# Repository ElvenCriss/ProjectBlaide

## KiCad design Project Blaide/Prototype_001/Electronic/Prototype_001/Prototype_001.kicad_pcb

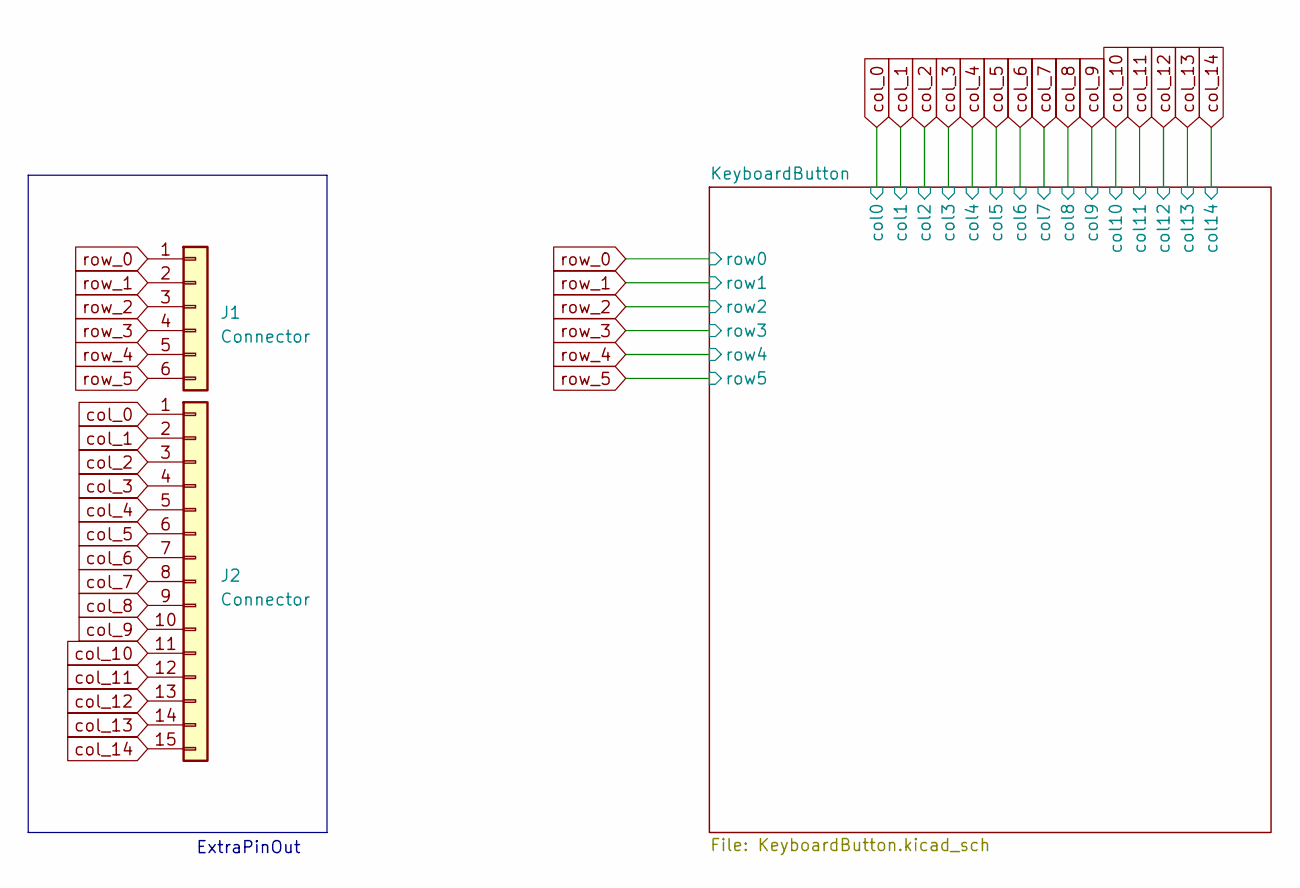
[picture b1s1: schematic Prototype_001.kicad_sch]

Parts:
J1: Connector; PinHeader_1x06_P2.54mm_Vertical
J2: Connector; PinHeader_1x15_P2.54mm_Vertical

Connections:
col_0: J2.1; also elsewhere on the board
col_1: J2.2; also elsewhere on the board
col_2: J2.3; also elsewhere on the board
col_3: J2.4; also elsewhere on the board
col_4: J2.5; also elsewhere on the board
col_5: J2.6; also elsewhere on the board
col_6: J2.7; also elsewhere on the board
col_7: J2.8; also elsewhere on the board
col_8: J2.9; also elsewhere on the board
col_9: J2.10; also elsewhere on the board
col_10: J2.11; also elsewhere on the board
col_11: J2.12; also elsewhere on the board
col_12: J2.13; also elsewhere on the board
col_13: J2.14; also elsewhere on the board
col_14: J2.15; also elsewhere on the board
row_0: J1.1; also elsewhere on the board
row_1: J1.2; also elsewhere on the board
row_2: J1.3; also elsewhere on the board
row_3: J1.4; also elsewhere on the board
row_4: J1.5; also elsewhere on the board
row_5: J1.6; also elsewhere on the board

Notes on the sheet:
ExtraPinOut

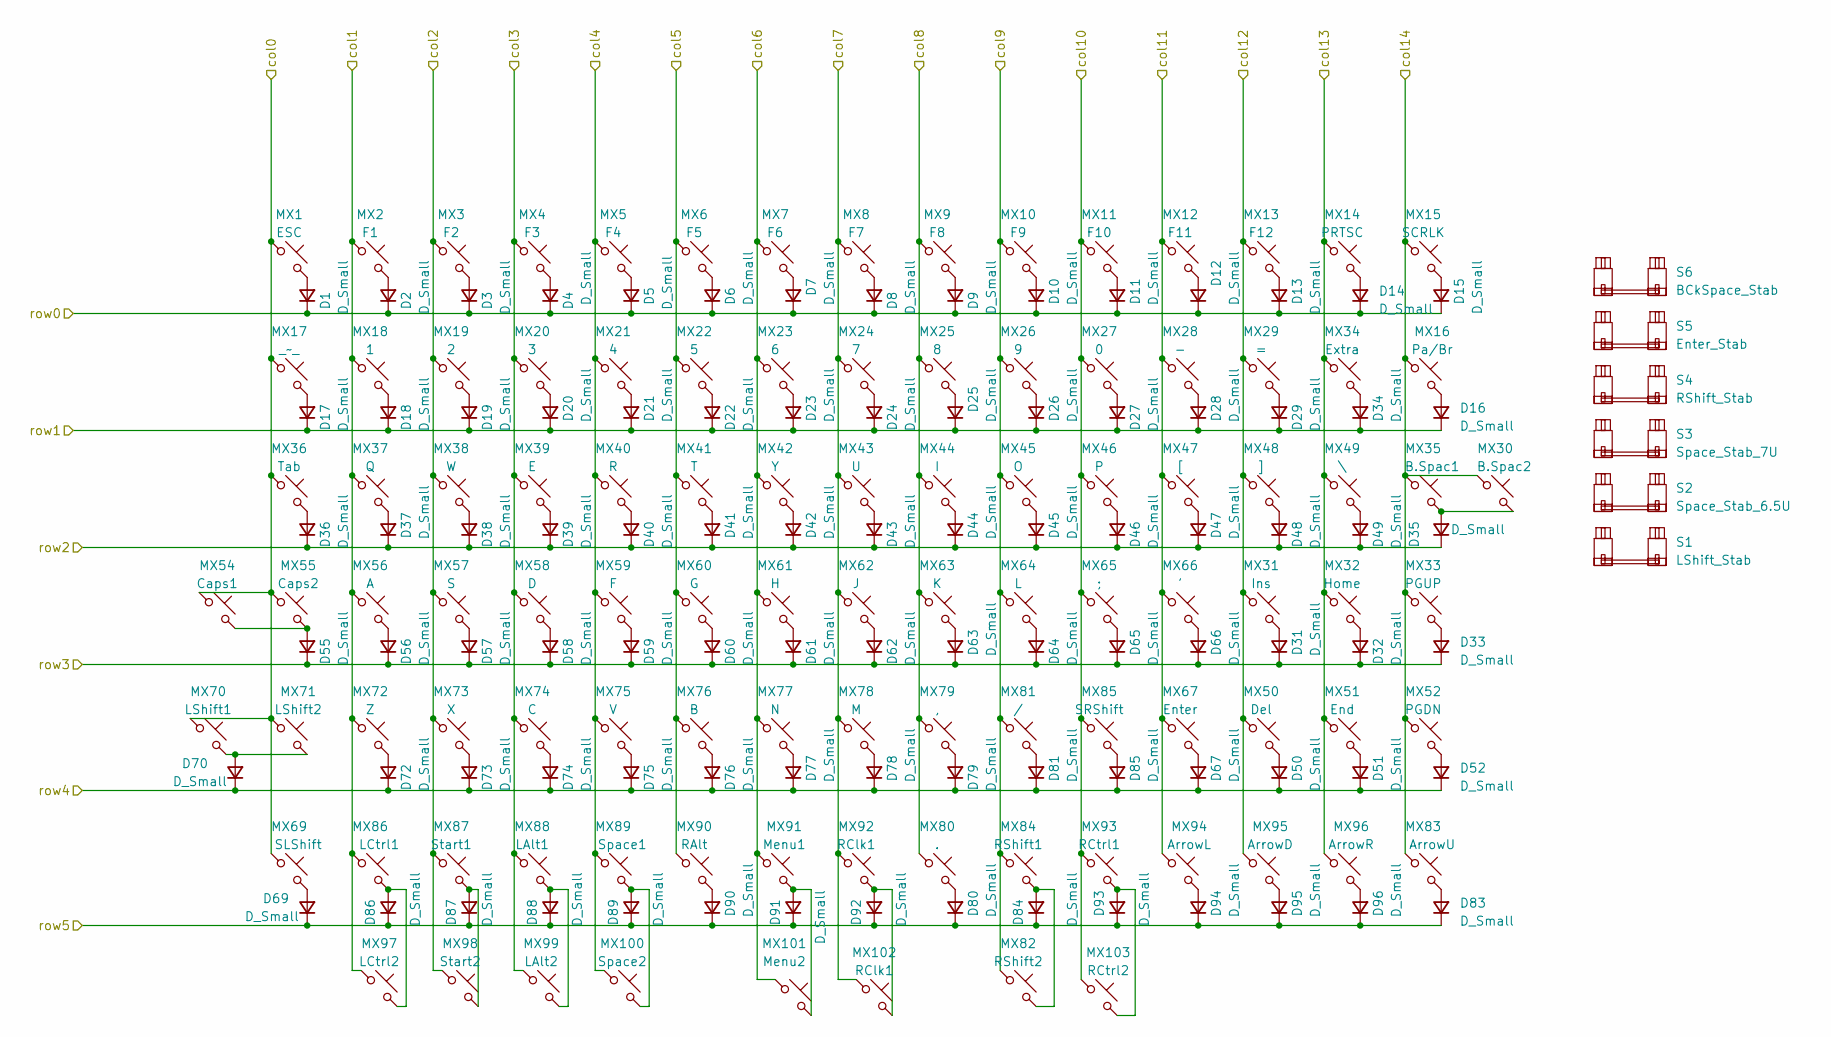
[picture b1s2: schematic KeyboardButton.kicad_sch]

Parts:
D1, D2, D3, D4, D5, D6, D7, D8, D9, D10, D11, D12, D13, D14, D15, D16, D17, D18, D19, D20, D21, D22, D23, D24, D25, D26, D27, D28, D29, D31, D32, D33, D34, D35, D36, D37, D38, D39, D40, D41, D42, D43, D44, D45, D46, D47, D48, D49, D50, D51, D52, D55, D56, D57, D58, D59, D60, D61, D62, D63, D64, D65, D66, D67, D69, D70, D72, D73, D74, D75, D76, D77, D78, D79, D80, D81, D83, D84, D85, D86, D87, D88, D89, D90, D91, D92, D93, D94, D95, D96: D_Small; D_SOD-123
MX1: ESC; SW_MX_HS_S_1u
MX2: F1; SW_MX_HS_S_1u
MX3: F2; SW_MX_HS_S_1u
MX4: F3; SW_MX_HS_S_1u
MX5: F4; SW_MX_HS_S_1u
MX6: F5; SW_MX_HS_S_1u
MX7: F6; SW_MX_HS_S_1u
MX8: F7; SW_MX_HS_S_1u
MX9: F8; SW_MX_HS_S_1u
MX10: F9; SW_MX_HS_S_1u
MX11: F10; SW_MX_HS_S_1u
MX12: F11; SW_MX_HS_S_1u
MX13: F12; SW_MX_HS_S_1u
MX14: PRTSC; SW_MX_HS_S_1u
MX15: SCRLK; SW_MX_HS_S_1u
MX16: Pa/Br; SW_MX_HS_S_1u
MX17: _~_; SW_MX_HS_S_1u
MX18: 1; SW_MX_HS_S_1u
MX19: 2; SW_MX_HS_S_1u
MX20: 3; SW_MX_HS_S_1u
MX21: 4; SW_MX_HS_S_1u
MX22: 5; SW_MX_HS_S_1u
MX23: 6; SW_MX_HS_S_1u
MX24: 7; SW_MX_HS_S_1u
MX25: 8; SW_MX_HS_S_1u
MX26: 9; SW_MX_HS_S_1u
MX27: 0; SW_MX_HS_S_1u
MX28: -; SW_MX_HS_S_1u
MX29: =; SW_MX_HS_S_1u
MX30: B.Spac2; SW_MX_HS_S_1u
MX31: Ins; SW_MX_HS_S_1u
MX32: Home; SW_MX_HS_S_1u
MX33: PGUP; SW_MX_HS_S_1u
MX34: Extra; SW_MX_HS_S_1u
MX35: B.Spac1; SW_MX_HS_S_1u
MX36: Tab; SW_MX_HS_1.5u
MX37: Q; SW_MX_HS_S_1u
MX38: W; SW_MX_HS_S_1u
MX39: E; SW_MX_HS_S_1u
MX40: R; SW_MX_HS_S_1u
MX41: T; SW_MX_HS_S_1u
MX42: Y; SW_MX_HS_S_1u
MX43: U; SW_MX_HS_S_1u
MX44: I; SW_MX_HS_S_1u
MX45: O; SW_MX_HS_S_1u
MX46: P; SW_MX_HS_S_1u
MX47: [; SW_MX_HS_S_1u
MX48: ]; SW_MX_HS_S_1u
MX49: \; SW_MX_HS_1.5u
MX50: Del; SW_MX_HS_S_1u
MX51: End; SW_MX_HS_S_1u
MX52: PGDN; SW_MX_HS_S_1u
MX54: Caps1; SW_MX_HS_1.75u_STP_1.25
MX55: Caps2; SW_MX_HS_1.75u
MX56: A; SW_MX_HS_S_1u
MX57: S; SW_MX_HS_S_1u
MX58: D; SW_MX_HS_S_1u
MX59: F; SW_MX_HS_S_1u
MX60: G; SW_MX_HS_S_1u
MX61: H; SW_MX_HS_S_1u
MX62: J; SW_MX_HS_S_1u
MX63: K; SW_MX_HS_S_1u
MX64: L; SW_MX_HS_S_1u
MX65: ;; SW_MX_HS_S_1u
MX66: '; SW_MX_HS_S_1u
MX67: Enter; SW_MX_HS_S_1u
MX69: SLShift; SW_MX_HS_1.25u
MX70: LShift1; SW_MX_HS_S_1u
MX71: LShift2; SW_MX_HS_S_1u
MX72: Z; SW_MX_HS_S_1u
MX73: X; SW_MX_HS_S_1u
MX74: C; SW_MX_HS_S_1u
MX75: V; SW_MX_HS_S_1u
MX76: B; SW_MX_HS_S_1u
MX77: N; SW_MX_HS_S_1u
MX78: M; SW_MX_HS_S_1u
MX79: ,; SW_MX_HS_S_1u
MX80: .; SW_MX_HS_S_1u
MX81: /; SW_MX_HS_S_1u
MX82: RShift2; SW_MX_HS_S_1u
MX83: ArrowU; SW_MX_HS_S_1u
MX84: RShift1; SW_MX_HS_1.75u
MX85: SRShift; SW_MX_HS_S_1u
MX86: LCtrl1; SW_MX_HS_1.25u
MX87: Start1; SW_MX_HS_1.25u
MX88: LAlt1; SW_MX_HS_1.25u
MX89: Space1; SW_MX_HS_S_1u
MX90: RAlt; SW_MX_HS_1.25u
MX91: Menu1; SW_MX_HS_1.25u
MX92: RClk1; SW_MX_HS_1.25u
MX93: RCtrl1; SW_MX_HS_1.25u
MX94: ArrowL; SW_MX_HS_S_1u
MX95: ArrowD; SW_MX_HS_S_1u
MX96: ArrowR; SW_MX_HS_S_1u
MX97: LCtrl2; SW_MX_HS_1.5u
MX98: Start2; SW_MX_HS_1.5u
MX99: LAlt2; SW_MX_HS_1.5u
MX100: Space2; SW_MX_HS_S_1u
MX101: Menu2; SW_MX_HS_1.5u
MX102: RClk1; SW_MX_HS_1.5u
MX103: RCtrl2; SW_MX_HS_1.5u
S1: LShift_Stab; STAB_MX_2.25u
S2: Space_Stab_6.5U; STAB_MX_P_6.25u
S3: Space_Stab_7U; STAB_MX_P_7u
S4: RShift_Stab; STAB_MX_P_2.75u
S5: Enter_Stab; STAB_MX_P_2.25u
S6: BCkSpace_Stab; STAB_MX_P_2u

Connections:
unnamed: D1.2 (A), MX1.2
unnamed: D2.2 (A), MX2.2
unnamed: D3.2 (A), MX3.2
unnamed: D4.2 (A), MX4.2
unnamed: D5.2 (A), MX5.2
unnamed: D6.2 (A), MX6.2
unnamed: D7.2 (A), MX7.2
unnamed: D8.2 (A), MX8.2
unnamed: D9.2 (A), MX9.2
unnamed: D10.2 (A), MX10.2
unnamed: D11.2 (A), MX11.2
unnamed: D12.2 (A), MX12.2
unnamed: D13.2 (A), MX13.2
unnamed: D14.2 (A), MX14.2
unnamed: D15.2 (A), MX15.2
unnamed: D16.2 (A), MX16.2
unnamed: D17.2 (A), MX17.2
unnamed: D18.2 (A), MX18.2
unnamed: D19.2 (A), MX19.2
unnamed: D20.2 (A), MX20.2
unnamed: D21.2 (A), MX21.2
unnamed: D22.2 (A), MX22.2
unnamed: D23.2 (A), MX23.2
unnamed: D24.2 (A), MX24.2
unnamed: D25.2 (A), MX25.2
unnamed: D26.2 (A), MX26.2
unnamed: D27.2 (A), MX27.2
unnamed: D28.2 (A), MX28.2
unnamed: D29.2 (A), MX29.2
unnamed: D31.2 (A), MX31.2
unnamed: D32.2 (A), MX32.2
unnamed: D33.2 (A), MX33.2
unnamed: D34.2 (A), MX34.2
unnamed: D35.2 (A), MX30.2, MX35.2
unnamed: D36.2 (A), MX36.2
unnamed: D37.2 (A), MX37.2
unnamed: D38.2 (A), MX38.2
unnamed: D39.2 (A), MX39.2
unnamed: D40.2 (A), MX40.2
unnamed: D41.2 (A), MX41.2
unnamed: D42.2 (A), MX42.2
unnamed: D43.2 (A), MX43.2
unnamed: D44.2 (A), MX44.2
unnamed: D45.2 (A), MX45.2
unnamed: D46.2 (A), MX46.2
unnamed: D47.2 (A), MX47.2
unnamed: D48.2 (A), MX48.2
unnamed: D49.2 (A), MX49.2
unnamed: D50.2 (A), MX50.2
unnamed: D51.2 (A), MX51.2
unnamed: D52.2 (A), MX52.2
unnamed: D55.2 (A), MX54.2, MX55.2
unnamed: D56.2 (A), MX56.2
unnamed: D57.2 (A), MX57.2
unnamed: D58.2 (A), MX58.2
unnamed: D59.2 (A), MX59.2
unnamed: D60.2 (A), MX60.2
unnamed: D61.2 (A), MX61.2
unnamed: D62.2 (A), MX62.2
unnamed: D63.2 (A), MX63.2
unnamed: D64.2 (A), MX64.2
unnamed: D65.2 (A), MX65.2
unnamed: D66.2 (A), MX66.2
unnamed: D67.2 (A), MX67.2
unnamed: D69.2 (A), MX69.2
unnamed: D70.2 (A), MX70.2, MX71.2
unnamed: D72.2 (A), MX72.2
unnamed: D73.2 (A), MX73.2
unnamed: D74.2 (A), MX74.2
unnamed: D75.2 (A), MX75.2
unnamed: D76.2 (A), MX76.2
unnamed: D77.2 (A), MX77.2
unnamed: D78.2 (A), MX78.2
unnamed: D79.2 (A), MX79.2
unnamed: D80.2 (A), MX80.2
unnamed: D81.2 (A), MX81.2
unnamed: D83.2 (A), MX83.2
unnamed: D84.2 (A), MX82.2, MX84.2
unnamed: D85.2 (A), MX85.2
unnamed: D86.2 (A), MX86.2, MX97.2
unnamed: D87.2 (A), MX87.2, MX98.2
unnamed: D88.2 (A), MX88.2, MX99.2
unnamed: D89.2 (A), MX89.2, MX100.2
unnamed: D90.2 (A), MX90.2
unnamed: D91.2 (A), MX91.2, MX101.2
unnamed: D92.2 (A), MX92.2, MX102.2
unnamed: D93.2 (A), MX93.2, MX103.2
unnamed: D94.2 (A), MX94.2
unnamed: D95.2 (A), MX95.2
unnamed: D96.2 (A), MX96.2
col_0: MX1.1, MX17.1, MX36.1, MX54.1, MX55.1, MX69.1, MX70.1, MX71.1; also elsewhere on the board
col_1: MX2.1, MX18.1, MX37.1, MX56.1, MX72.1, MX86.1, MX97.1; also elsewhere on the board
col_2: MX3.1, MX19.1, MX38.1, MX57.1, MX73.1, MX87.1, MX98.1; also elsewhere on the board
col_3: MX4.1, MX20.1, MX39.1, MX58.1, MX74.1, MX88.1, MX99.1; also elsewhere on the board
col_4: MX5.1, MX21.1, MX40.1, MX59.1, MX75.1, MX89.1, MX100.1; also elsewhere on the board
col_5: MX6.1, MX22.1, MX41.1, MX60.1, MX76.1, MX90.1; also elsewhere on the board
col_6: MX7.1, MX23.1, MX42.1, MX61.1, MX77.1, MX91.1, MX101.1; also elsewhere on the board
col_7: MX8.1, MX24.1, MX43.1, MX62.1, MX78.1, MX92.1, MX102.1; also elsewhere on the board
col_8: MX9.1, MX25.1, MX44.1, MX63.1, MX79.1, MX80.1; also elsewhere on the board
col_9: MX10.1, MX26.1, MX45.1, MX64.1, MX81.1, MX82.1, MX84.1; also elsewhere on the board
col_10: MX11.1, MX27.1, MX46.1, MX65.1, MX85.1, MX93.1, MX103.1; also elsewhere on the board
col_11: MX12.1, MX28.1, MX47.1, MX66.1, MX67.1, MX94.1; also elsewhere on the board
col_12: MX13.1, MX29.1, MX31.1, MX48.1, MX50.1, MX95.1; also elsewhere on the board
col_13: MX14.1, MX32.1, MX34.1, MX49.1, MX51.1, MX96.1; also elsewhere on the board
col_14: MX15.1, MX16.1, MX30.1, MX33.1, MX35.1, MX52.1, MX83.1; also elsewhere on the board
row_0: D1.1 (K), D2.1 (K), D3.1 (K), D4.1 (K), D5.1 (K), D6.1 (K), D7.1 (K), D8.1 (K), D9.1 (K), D10.1 (K), D11.1 (K), D12.1 (K), D13.1 (K), D14.1 (K), D15.1 (K); also elsewhere on the board
row_1: D16.1 (K), D17.1 (K), D18.1 (K), D19.1 (K), D20.1 (K), D21.1 (K), D22.1 (K), D23.1 (K), D24.1 (K), D25.1 (K), D26.1 (K), D27.1 (K), D28.1 (K), D29.1 (K), D34.1 (K); also elsewhere on the board
row_2: D35.1 (K), D36.1 (K), D37.1 (K), D38.1 (K), D39.1 (K), D40.1 (K), D41.1 (K), D42.1 (K), D43.1 (K), D44.1 (K), D45.1 (K), D46.1 (K), D47.1 (K), D48.1 (K), D49.1 (K); also elsewhere on the board
row_3: D31.1 (K), D32.1 (K), D33.1 (K), D55.1 (K), D56.1 (K), D57.1 (K), D58.1 (K), D59.1 (K), D60.1 (K), D61.1 (K), D62.1 (K), D63.1 (K), D64.1 (K), D65.1 (K), D66.1 (K); also elsewhere on the board
row_4: D50.1 (K), D51.1 (K), D52.1 (K), D67.1 (K), D70.1 (K), D72.1 (K), D73.1 (K), D74.1 (K), D75.1 (K), D76.1 (K), D77.1 (K), D78.1 (K), D79.1 (K), D81.1 (K), D85.1 (K); also elsewhere on the board
row_5: D69.1 (K), D80.1 (K), D83.1 (K), D84.1 (K), D86.1 (K), D87.1 (K), D88.1 (K), D89.1 (K), D90.1 (K), D91.1 (K), D92.1 (K), D93.1 (K), D94.1 (K), D95.1 (K), D96.1 (K); also elsewhere on the board

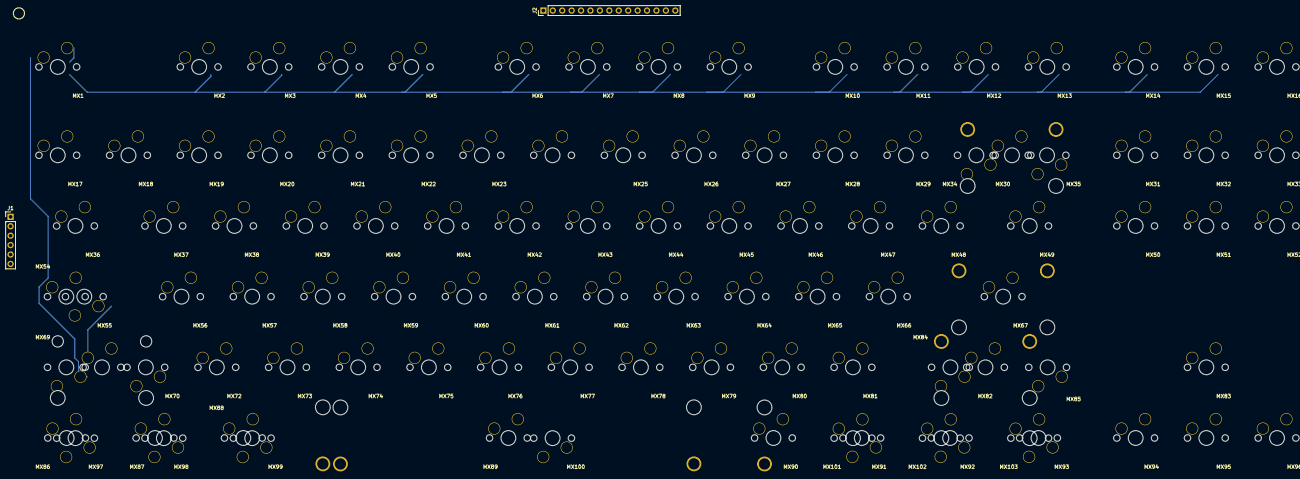
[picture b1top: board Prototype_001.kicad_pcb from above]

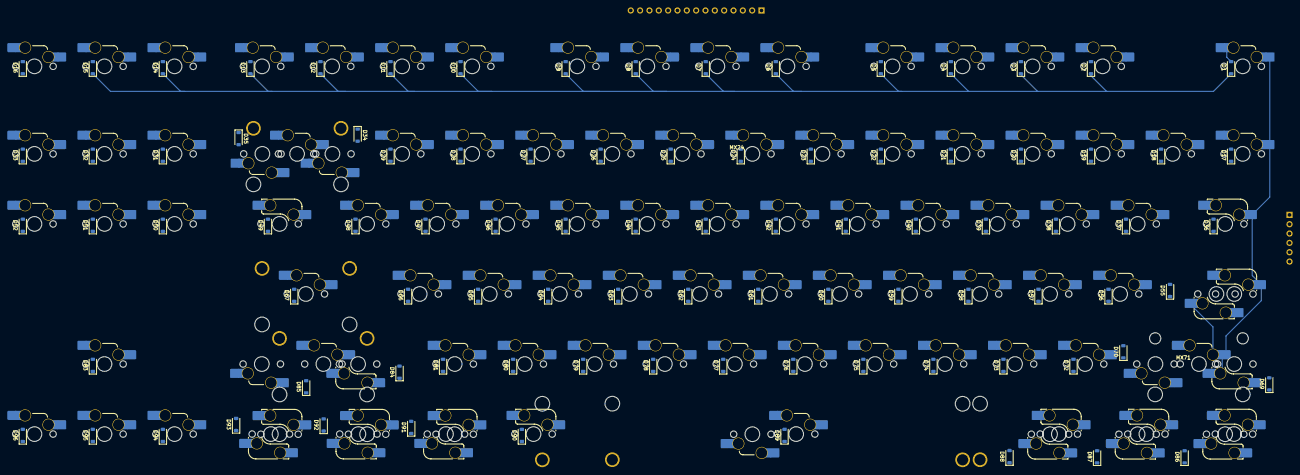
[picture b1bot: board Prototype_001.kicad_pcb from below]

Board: 2 copper layers, 199 parts (191 on the bottom side), 111 nets.

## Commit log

2024-05-12 Add files via upload
    First Commit!!
2024-05-25 DecisionMaking
2024-05-30 Ivan - First Commit
    1.)added all previous design footprint and component
2024-07-08 Ivan - Update: v0.0.0.1 - Finalizing electronic Board
